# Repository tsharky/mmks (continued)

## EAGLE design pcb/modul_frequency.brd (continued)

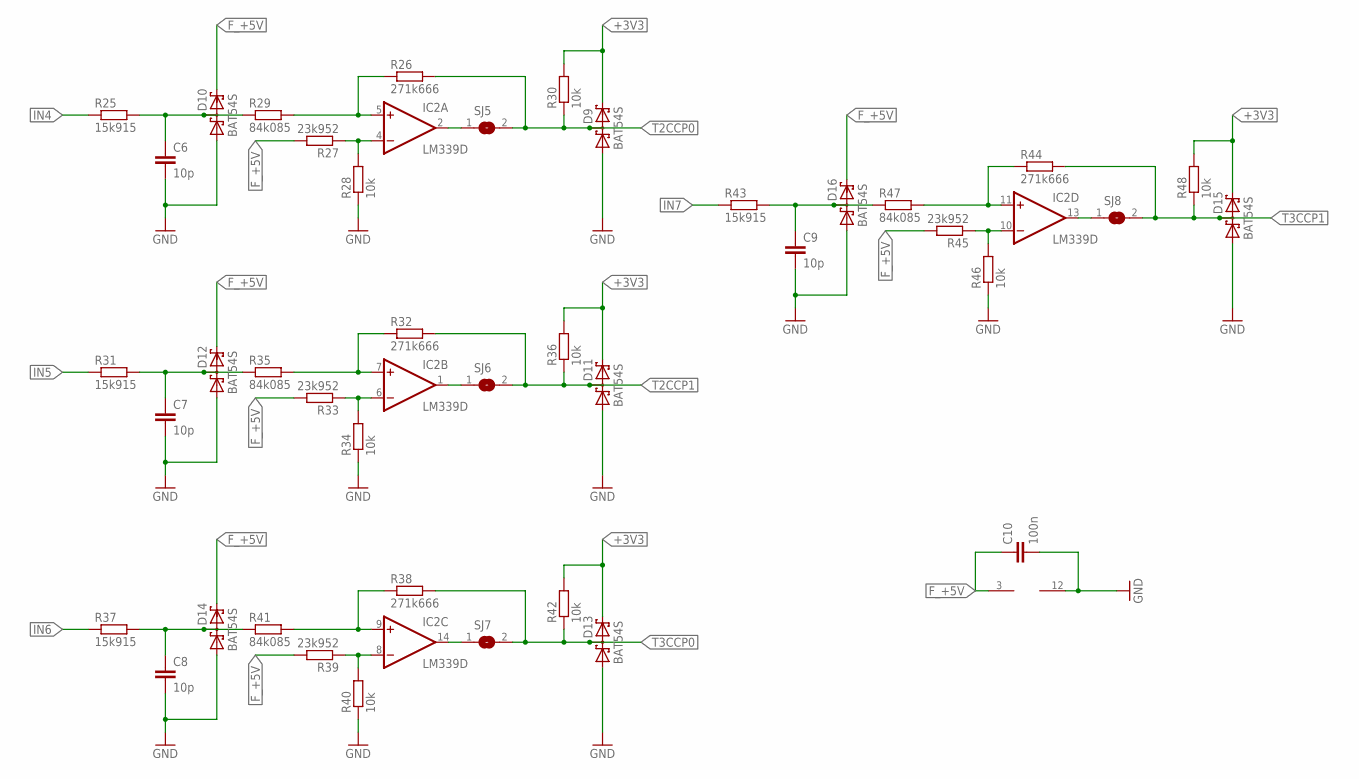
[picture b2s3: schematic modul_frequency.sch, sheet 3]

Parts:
C6, C7, C8, C9: 10p; C0805
C10: 100n; C0805
D9, D10, D11, D12, D13, D14, D15, D16: BAT54S; SOT23
IC2: LM339D; SO14
R25, R31, R37, R43: 15k915; R0805
R26, R32, R38, R44: 271k666; R0805
R27, R33, R39, R45: 23k952; R0805
R28, R30, R34, R36, R40, R42, R46, R48: 10k; R0805
R29, R35, R41, R47: 84k085; R0805
SJ5, SJ6, SJ7, SJ8: SJ

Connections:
+3V3: D9.2 (C2), D11.2 (C2), D13.2 (C2), D15.2 (C2), R30.2, R36.2, R42.2, R48.2; also elsewhere on the board
F_+5V: C10.1, D10.2 (C2), D12.2 (C2), D14.2 (C2), D16.2 (C2), IC2.3 (V+), R27.2, R33.2, R39.2, R45.2; also elsewhere on the board
GND: C6.2, C7.2, C8.2, C9.2, C10.2, D9.1 (A1), D10.1 (A1), D11.1 (A1), D12.1 (A1), D13.1 (A1), D14.1 (A1), D15.1 (A1), D16.1 (A1), IC2.12 (GND), R28.1, R34.1, R40.1, R46.1; also elsewhere on the board
IN4: R25.1; also elsewhere on the board
IN5: R31.1; also elsewhere on the board
IN6: R37.1; also elsewhere on the board
IN7: R43.1; also elsewhere on the board
unnamed: IC2.5 (+IN), R26.1, R29.2
unnamed: IC2.4 (-IN), R27.1, R28.2
unnamed: C6.1, D10.3 (C1A2), R25.2, R29.1
unnamed: IC2.7 (+IN), R32.1, R35.2
unnamed: IC2.6 (-IN), R33.1, R34.2
unnamed: C7.1, D12.3 (C1A2), R31.2, R35.1
unnamed: IC2.1 (OUT), SJ6.1
unnamed: IC2.9 (+IN), R38.1, R41.2
unnamed: IC2.8 (-IN), R39.1, R40.2
unnamed: C8.1, D14.3 (C1A2), R37.2, R41.1
unnamed: IC2.14 (OUT), SJ7.1
unnamed: IC2.11 (+IN), R44.1, R47.2
unnamed: IC2.10 (-IN), R45.1, R46.2
unnamed: C9.1, D16.3 (C1A2), R43.2, R47.1
unnamed: IC2.13 (OUT), SJ8.1
unnamed: IC2.2 (OUT), SJ5.1
T2CCP0: D9.3 (C1A2), R26.2, R30.1, SJ5.2; also elsewhere on the board
T2CCP1: D11.3 (C1A2), R32.2, R36.1, SJ6.2; also elsewhere on the board
T3CCP0: D13.3 (C1A2), R38.2, R42.1, SJ7.2; also elsewhere on the board
T3CCP1: D15.3 (C1A2), R44.2, R48.1, SJ8.2; also elsewhere on the board

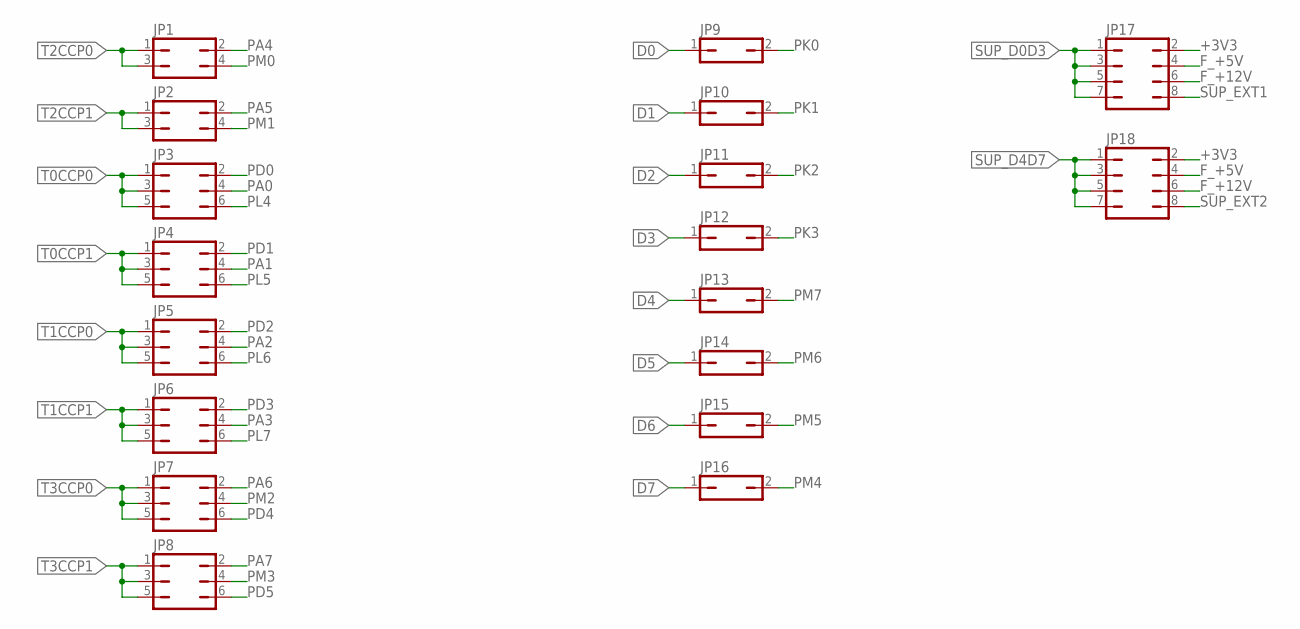
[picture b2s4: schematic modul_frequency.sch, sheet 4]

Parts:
JP1, JP2: JP2Q
JP3, JP4, JP5, JP6, JP7, JP8: JP3Q
JP9, JP10, JP11, JP12, JP13, JP14, JP15, JP16: JP1Q; JP1
JP17, JP18: JP4Q

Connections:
+3V3: JP17.2, JP18.2; also elsewhere on the board
D0: JP9.1; also elsewhere on the board
D1: JP10.1; also elsewhere on the board
D2: JP11.1; also elsewhere on the board
D3: JP12.1; also elsewhere on the board
D4: JP13.1; also elsewhere on the board
D5: JP14.1; also elsewhere on the board
D6: JP15.1; also elsewhere on the board
D7: JP16.1; also elsewhere on the board
F_+5V: JP17.4, JP18.4; also elsewhere on the board
F_+12V: JP17.6, JP18.6; also elsewhere on the board
PA0: JP3.4; also elsewhere on the board
PA1: JP4.4; also elsewhere on the board
PA2: JP5.4; also elsewhere on the board
PA3: JP6.4; also elsewhere on the board
PA4: JP1.2; also elsewhere on the board
PA5: JP2.2; also elsewhere on the board
PA6: JP7.2; also elsewhere on the board
PA7: JP8.2; also elsewhere on the board
PD0: JP3.2; also elsewhere on the board
PD1: JP4.2; also elsewhere on the board
PD2: JP5.2; also elsewhere on the board
PD3: JP6.2; also elsewhere on the board
PD4: JP7.6; also elsewhere on the board
PD5: JP8.6; also elsewhere on the board
PK0: JP9.2; also elsewhere on the board
PK1: JP10.2; also elsewhere on the board
PK2: JP11.2; also elsewhere on the board
PK3: JP12.2; also elsewhere on the board
PL4: JP3.6; also elsewhere on the board
PL5: JP4.6; also elsewhere on the board
PL6: JP5.6
PL7: JP6.6
PM0: JP1.4; also elsewhere on the board
PM1: JP2.4; also elsewhere on the board
PM2: JP7.4; also elsewhere on the board
PM3: JP8.4; also elsewhere on the board
PM4: JP16.2; also elsewhere on the board
PM5: JP15.2; also elsewhere on the board
PM6: JP14.2; also elsewhere on the board
PM7: JP13.2; also elsewhere on the board
SUP_D0D3: JP17.1, JP17.3, JP17.5, JP17.7; also elsewhere on the board
SUP_D4D7: JP18.1, JP18.3, JP18.5, JP18.7; also elsewhere on the board
SUP_EXT1: JP17.8; also elsewhere on the board
SUP_EXT2: JP18.8; also elsewhere on the board
T0CCP0: JP3.1, JP3.3, JP3.5; also elsewhere on the board
T0CCP1: JP4.1, JP4.3, JP4.5; also elsewhere on the board
T1CCP0: JP5.1, JP5.3, JP5.5; also elsewhere on the board
T1CCP1: JP6.1, JP6.3, JP6.5; also elsewhere on the board
T2CCP0: JP1.1, JP1.3; also elsewhere on the board
T2CCP1: JP2.1, JP2.3; also elsewhere on the board
T3CCP0: JP7.1, JP7.3, JP7.5; also elsewhere on the board
T3CCP1: JP8.1, JP8.3, JP8.5; also elsewhere on the board

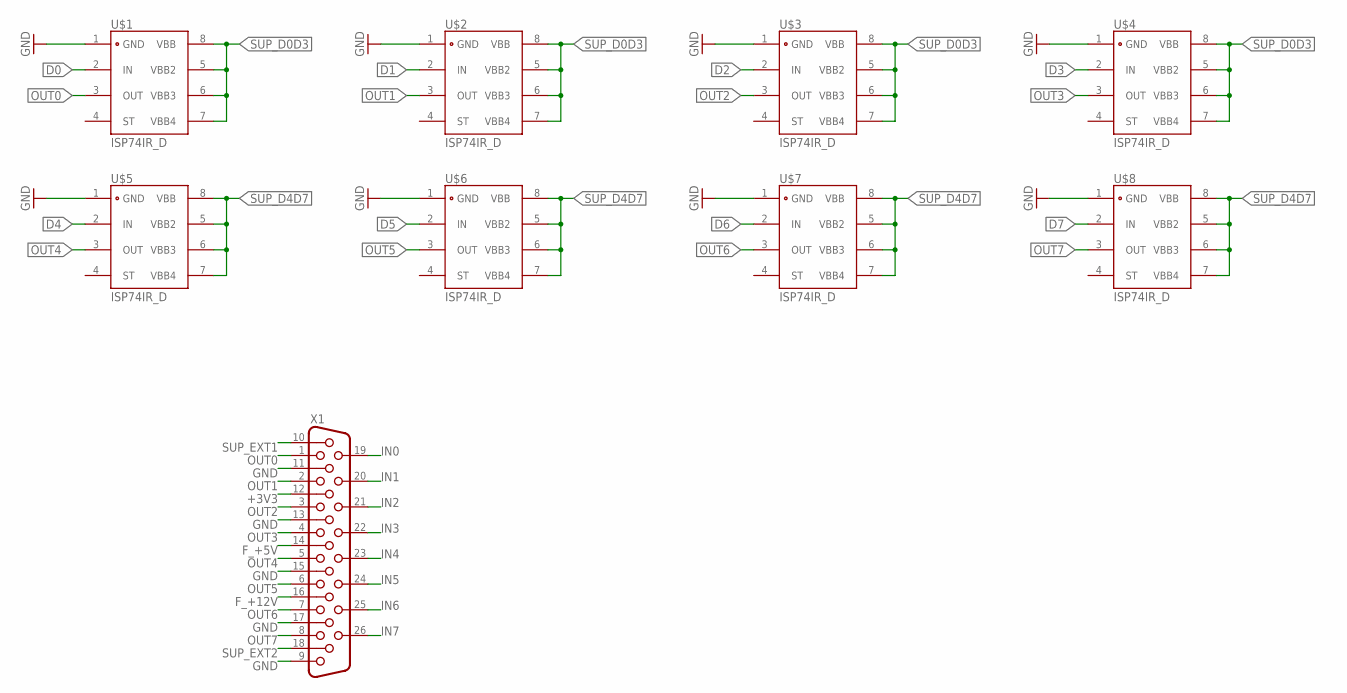
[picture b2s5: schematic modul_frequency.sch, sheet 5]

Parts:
U$1, U$2, U$3, U$4, U$5, U$6, U$7, U$8: ISP74IR_D; SO08
X1: HF26H; HDF26H

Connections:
+3V3: X1.12; also elsewhere on the board
D0: U$1.2 (IN); also elsewhere on the board
D1: U$2.2 (IN); also elsewhere on the board
D2: U$3.2 (IN); also elsewhere on the board
D3: U$4.2 (IN); also elsewhere on the board
D4: U$5.2 (IN); also elsewhere on the board
D5: U$6.2 (IN); also elsewhere on the board
D6: U$7.2 (IN); also elsewhere on the board
D7: U$8.2 (IN); also elsewhere on the board
F_+5V: X1.14; also elsewhere on the board
F_+12V: X1.16; also elsewhere on the board
GND: U$1.1 (GND), U$2.1 (GND), U$3.1 (GND), U$4.1 (GND), U$5.1 (GND), U$6.1 (GND), U$7.1 (GND), U$8.1 (GND), X1.9, X1.11, X1.13, X1.15, X1.17; also elsewhere on the board
IN0: X1.19; also elsewhere on the board
IN1: X1.20; also elsewhere on the board
IN2: X1.21; also elsewhere on the board
IN3: X1.22; also elsewhere on the board
IN4: X1.23; also elsewhere on the board
IN5: X1.24; also elsewhere on the board
IN6: X1.25; also elsewhere on the board
IN7: X1.26; also elsewhere on the board
OUT0: U$1.3 (OUT), X1.1
OUT1: U$2.3 (OUT), X1.2
OUT2: U$3.3 (OUT), X1.3
OUT3: U$4.3 (OUT), X1.4
OUT4: U$5.3 (OUT), X1.5
OUT5: U$6.3 (OUT), X1.6
OUT6: U$7.3 (OUT), X1.7
OUT7: U$8.3 (OUT), X1.8
SUP_D0D3: U$1.5 (VBB2), U$1.6 (VBB3), U$1.7 (VBB4), U$1.8 (VBB), U$2.5 (VBB2), U$2.6 (VBB3), U$2.7 (VBB4), U$2.8 (VBB), U$3.5 (VBB2), U$3.6 (VBB3), U$3.7 (VBB4), U$3.8 (VBB), U$4.5 (VBB2), U$4.6 (VBB3), U$4.7 (VBB4), U$4.8 (VBB); also elsewhere on the board
SUP_D4D7: U$5.5 (VBB2), U$5.6 (VBB3), U$5.7 (VBB4), U$5.8 (VBB), U$6.5 (VBB2), U$6.6 (VBB3), U$6.7 (VBB4), U$6.8 (VBB), U$7.5 (VBB2), U$7.6 (VBB3), U$7.7 (VBB4), U$7.8 (VBB), U$8.5 (VBB2), U$8.6 (VBB3), U$8.7 (VBB4), U$8.8 (VBB); also elsewhere on the board
SUP_EXT1: X1.10; also elsewhere on the board
SUP_EXT2: X1.18; also elsewhere on the board

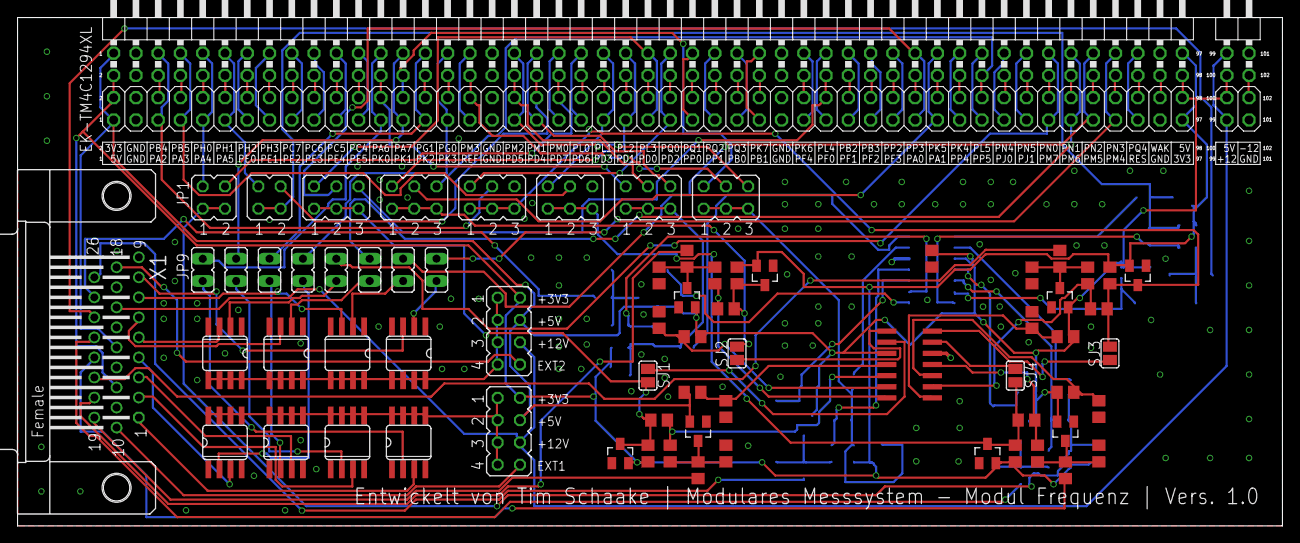
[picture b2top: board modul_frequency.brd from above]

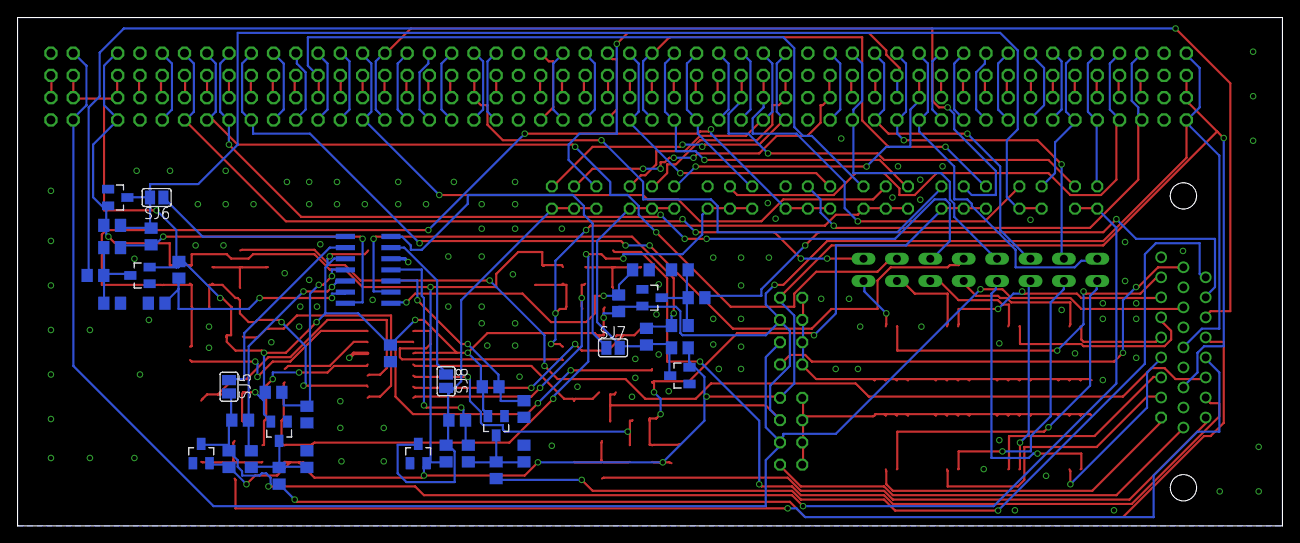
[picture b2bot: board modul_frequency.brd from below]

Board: 2 copper layers, 144.3 x 58.0 mm, 113 parts (42 on the bottom side), 160 nets.

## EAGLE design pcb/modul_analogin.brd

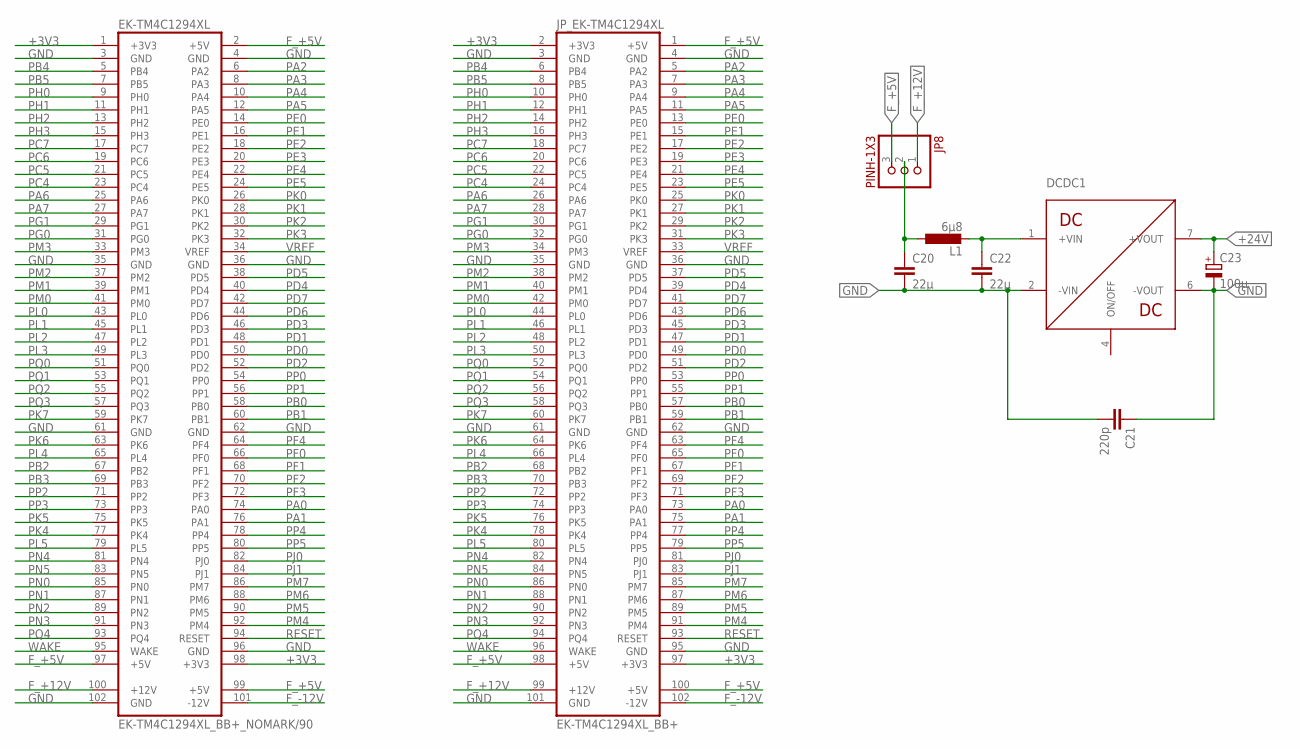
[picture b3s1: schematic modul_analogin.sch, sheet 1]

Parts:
C20, C22: 22µ; C1206
C21: 220p; C1808
C23: 100µ; E2,5-6
DCDC1: TDN3WI; TDN_XWI
EK-TM4C1294XL: EK-TM4C1294XL_BB+_NOMARK/90
JP8: PINH-1X3; 1X3
JP_EK-TM4C1294XL: EK-TM4C1294XL_BB+
L1: 6µ8; L1812

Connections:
+3V3: EK-TM4C1294XL.1 (+3V3), EK-TM4C1294XL.98 (+3V3), JP_EK-TM4C1294XL.2 (+3V3), JP_EK-TM4C1294XL.97 (+3V3); also elsewhere on the board
+24V: C23.+, DCDC1.7 (+VOUT); also elsewhere on the board
+VIN: C22.1, DCDC1.1 (+VIN), L1.2
F_+5V: EK-TM4C1294XL.2 (+5V), EK-TM4C1294XL.97 (+5V), EK-TM4C1294XL.99 (+5V), JP8.3, JP_EK-TM4C1294XL.1 (+5V), JP_EK-TM4C1294XL.98 (+5V), JP_EK-TM4C1294XL.100 (+5V); also elsewhere on the board
F_+12V: EK-TM4C1294XL.100 (+12V), JP8.1, JP_EK-TM4C1294XL.99 (+12V); also elsewhere on the board
F_-12V: EK-TM4C1294XL.101 (-12V), JP_EK-TM4C1294XL.102 (-12V); also elsewhere on the board
GND: C20.2, C21.1, C21.2, C22.2, C23.-, DCDC1.2 (-VIN), DCDC1.6 (-VOUT), EK-TM4C1294XL.3 (GND), EK-TM4C1294XL.4 (GND), EK-TM4C1294XL.35 (GND), EK-TM4C1294XL.36 (GND), EK-TM4C1294XL.61 (GND), EK-TM4C1294XL.62 (GND), EK-TM4C1294XL.96 (GND), EK-TM4C1294XL.102 (GND), JP_EK-TM4C1294XL.3 (GND), JP_EK-TM4C1294XL.4 (GND), JP_EK-TM4C1294XL.35 (GND), JP_EK-TM4C1294XL.36 (GND), JP_EK-TM4C1294XL.61 (GND), JP_EK-TM4C1294XL.62 (GND), JP_EK-TM4C1294XL.95 (GND), JP_EK-TM4C1294XL.101 (GND); also elsewhere on the board
unnamed: C20.1, JP8.2, L1.1
PA0: EK-TM4C1294XL.74 (PA0), JP_EK-TM4C1294XL.73 (PA0)
PA1: EK-TM4C1294XL.76 (PA1), JP_EK-TM4C1294XL.75 (PA1)
PA2: EK-TM4C1294XL.6 (PA2), JP_EK-TM4C1294XL.5 (PA2)
PA3: EK-TM4C1294XL.8 (PA3), JP_EK-TM4C1294XL.7 (PA3)
PA4: EK-TM4C1294XL.10 (PA4), JP_EK-TM4C1294XL.9 (PA4)
PA5: EK-TM4C1294XL.12 (PA5), JP_EK-TM4C1294XL.11 (PA5)
PA6: EK-TM4C1294XL.25 (PA6), JP_EK-TM4C1294XL.26 (PA6)
PA7: EK-TM4C1294XL.27 (PA7), JP_EK-TM4C1294XL.28 (PA7)
PB0: EK-TM4C1294XL.58 (PB0), JP_EK-TM4C1294XL.57 (PB0)
PB1: EK-TM4C1294XL.60 (PB1), JP_EK-TM4C1294XL.59 (PB1)
PB2: EK-TM4C1294XL.67 (PB2), JP_EK-TM4C1294XL.68 (PB2)
PB3: EK-TM4C1294XL.69 (PB3), JP_EK-TM4C1294XL.70 (PB3)
PB4: EK-TM4C1294XL.5 (PB4), JP_EK-TM4C1294XL.6 (PB4); also elsewhere on the board
PB5: EK-TM4C1294XL.7 (PB5), JP_EK-TM4C1294XL.8 (PB5); also elsewhere on the board
PC4: EK-TM4C1294XL.23 (PC4), JP_EK-TM4C1294XL.24 (PC4)
PC5: EK-TM4C1294XL.21 (PC5), JP_EK-TM4C1294XL.22 (PC5)
PC6: EK-TM4C1294XL.19 (PC6), JP_EK-TM4C1294XL.20 (PC6)
PC7: EK-TM4C1294XL.17 (PC7), JP_EK-TM4C1294XL.18 (PC7)
PD0: EK-TM4C1294XL.50 (PD0), JP_EK-TM4C1294XL.49 (PD0); also elsewhere on the board
PD1: EK-TM4C1294XL.48 (PD1), JP_EK-TM4C1294XL.47 (PD1); also elsewhere on the board
PD2: EK-TM4C1294XL.52 (PD2), JP_EK-TM4C1294XL.51 (PD2); also elsewhere on the board
PD3: EK-TM4C1294XL.46 (PD3), JP_EK-TM4C1294XL.45 (PD3); also elsewhere on the board
PD4: EK-TM4C1294XL.40 (PD4), JP_EK-TM4C1294XL.39 (PD4); also elsewhere on the board
PD5: EK-TM4C1294XL.38 (PD5), JP_EK-TM4C1294XL.37 (PD5); also elsewhere on the board
PD6: EK-TM4C1294XL.44 (PD6), JP_EK-TM4C1294XL.43 (PD6); also elsewhere on the board
PD7: EK-TM4C1294XL.42 (PD7), JP_EK-TM4C1294XL.41 (PD7); also elsewhere on the board
PE0: EK-TM4C1294XL.14 (PE0), JP_EK-TM4C1294XL.13 (PE0); also elsewhere on the board
PE1: EK-TM4C1294XL.16 (PE1), JP_EK-TM4C1294XL.15 (PE1); also elsewhere on the board
PE2: EK-TM4C1294XL.18 (PE2), JP_EK-TM4C1294XL.17 (PE2); also elsewhere on the board
PE3: EK-TM4C1294XL.20 (PE3), JP_EK-TM4C1294XL.19 (PE3); also elsewhere on the board
PE4: EK-TM4C1294XL.22 (PE4), JP_EK-TM4C1294XL.21 (PE4); also elsewhere on the board
PE5: EK-TM4C1294XL.24 (PE5), JP_EK-TM4C1294XL.23 (PE5); also elsewhere on the board
PF0: EK-TM4C1294XL.66 (PF0), JP_EK-TM4C1294XL.65 (PF0)
PF1: EK-TM4C1294XL.68 (PF1), JP_EK-TM4C1294XL.67 (PF1)
PF2: EK-TM4C1294XL.70 (PF2), JP_EK-TM4C1294XL.69 (PF2)
PF3: EK-TM4C1294XL.72 (PF3), JP_EK-TM4C1294XL.71 (PF3)
PF4: EK-TM4C1294XL.64 (PF4), JP_EK-TM4C1294XL.63 (PF4)
PG0: EK-TM4C1294XL.31 (PG0), JP_EK-TM4C1294XL.32 (PG0)
PG1: EK-TM4C1294XL.29 (PG1), JP_EK-TM4C1294XL.30 (PG1)
PH0: EK-TM4C1294XL.9 (PH0), JP_EK-TM4C1294XL.10 (PH0)
PH1: EK-TM4C1294XL.11 (PH1), JP_EK-TM4C1294XL.12 (PH1)
PH2: EK-TM4C1294XL.13 (PH2), JP_EK-TM4C1294XL.14 (PH2)
PH3: EK-TM4C1294XL.15 (PH3), JP_EK-TM4C1294XL.16 (PH3)
PJ0: EK-TM4C1294XL.82 (PJ0), JP_EK-TM4C1294XL.81 (PJ0)
PJ1: EK-TM4C1294XL.84 (PJ1), JP_EK-TM4C1294XL.83 (PJ1)
PK0: EK-TM4C1294XL.26 (PK0), JP_EK-TM4C1294XL.25 (PK0)
PK1: EK-TM4C1294XL.28 (PK1), JP_EK-TM4C1294XL.27 (PK1)
PK2: EK-TM4C1294XL.30 (PK2), JP_EK-TM4C1294XL.29 (PK2)
PK3: EK-TM4C1294XL.32 (PK3), JP_EK-TM4C1294XL.31 (PK3)
PK4: EK-TM4C1294XL.77 (PK4), JP_EK-TM4C1294XL.78 (PK4)
PK5: EK-TM4C1294XL.75 (PK5), JP_EK-TM4C1294XL.76 (PK5)
PK6: EK-TM4C1294XL.63 (PK6), JP_EK-TM4C1294XL.64 (PK6)
PK7: EK-TM4C1294XL.59 (PK7), JP_EK-TM4C1294XL.60 (PK7)
PL0: EK-TM4C1294XL.43 (PL0), JP_EK-TM4C1294XL.44 (PL0)
PL1: EK-TM4C1294XL.45 (PL1), JP_EK-TM4C1294XL.46 (PL1)
PL2: EK-TM4C1294XL.47 (PL2), JP_EK-TM4C1294XL.48 (PL2)
PL3: EK-TM4C1294XL.49 (PL3), JP_EK-TM4C1294XL.50 (PL3)
PL4: EK-TM4C1294XL.65 (PL4), JP_EK-TM4C1294XL.66 (PL4)
PL5: EK-TM4C1294XL.79 (PL5), JP_EK-TM4C1294XL.80 (PL5)
PM0: EK-TM4C1294XL.41 (PM0), JP_EK-TM4C1294XL.42 (PM0)
PM1: EK-TM4C1294XL.39 (PM1), JP_EK-TM4C1294XL.40 (PM1)
PM2: EK-TM4C1294XL.37 (PM2), JP_EK-TM4C1294XL.38 (PM2)
PM3: EK-TM4C1294XL.33 (PM3), JP_EK-TM4C1294XL.34 (PM3)
PM4: EK-TM4C1294XL.92 (PM4), JP_EK-TM4C1294XL.91 (PM4)
PM5: EK-TM4C1294XL.90 (PM5), JP_EK-TM4C1294XL.89 (PM5)
PM6: EK-TM4C1294XL.88 (PM6), JP_EK-TM4C1294XL.87 (PM6)
PM7: EK-TM4C1294XL.86 (PM7), JP_EK-TM4C1294XL.85 (PM7)
PN0: EK-TM4C1294XL.85 (PN0), JP_EK-TM4C1294XL.86 (PN0)
PN1: EK-TM4C1294XL.87 (PN1), JP_EK-TM4C1294XL.88 (PN1)
PN2: EK-TM4C1294XL.89 (PN2), JP_EK-TM4C1294XL.90 (PN2)
PN3: EK-TM4C1294XL.91 (PN3), JP_EK-TM4C1294XL.92 (PN3)
PN4: EK-TM4C1294XL.81 (PN4), JP_EK-TM4C1294XL.82 (PN4)
PN5: EK-TM4C1294XL.83 (PN5), JP_EK-TM4C1294XL.84 (PN5)
PP0: EK-TM4C1294XL.54 (PP0), JP_EK-TM4C1294XL.53 (PP0)
PP1: EK-TM4C1294XL.56 (PP1), JP_EK-TM4C1294XL.55 (PP1)
PP2: EK-TM4C1294XL.71 (PP2), JP_EK-TM4C1294XL.72 (PP2)
PP3: EK-TM4C1294XL.73 (PP3), JP_EK-TM4C1294XL.74 (PP3)
PP4: EK-TM4C1294XL.78 (PP4), JP_EK-TM4C1294XL.77 (PP4)
PP5: EK-TM4C1294XL.80 (PP5), JP_EK-TM4C1294XL.79 (PP5)
PQ0: EK-TM4C1294XL.51 (PQ0), JP_EK-TM4C1294XL.52 (PQ0)
PQ1: EK-TM4C1294XL.53 (PQ1), JP_EK-TM4C1294XL.54 (PQ1)
PQ2: EK-TM4C1294XL.55 (PQ2), JP_EK-TM4C1294XL.56 (PQ2)
PQ3: EK-TM4C1294XL.57 (PQ3), JP_EK-TM4C1294XL.58 (PQ3)
PQ4: EK-TM4C1294XL.93 (PQ4), JP_EK-TM4C1294XL.94 (PQ4)
RESET: EK-TM4C1294XL.94 (RESET), JP_EK-TM4C1294XL.93 (RESET)
VREF: EK-TM4C1294XL.34 (VREF), JP_EK-TM4C1294XL.33 (VREF)
WAKE: EK-TM4C1294XL.95 (WAKE), JP_EK-TM4C1294XL.96 (WAKE)

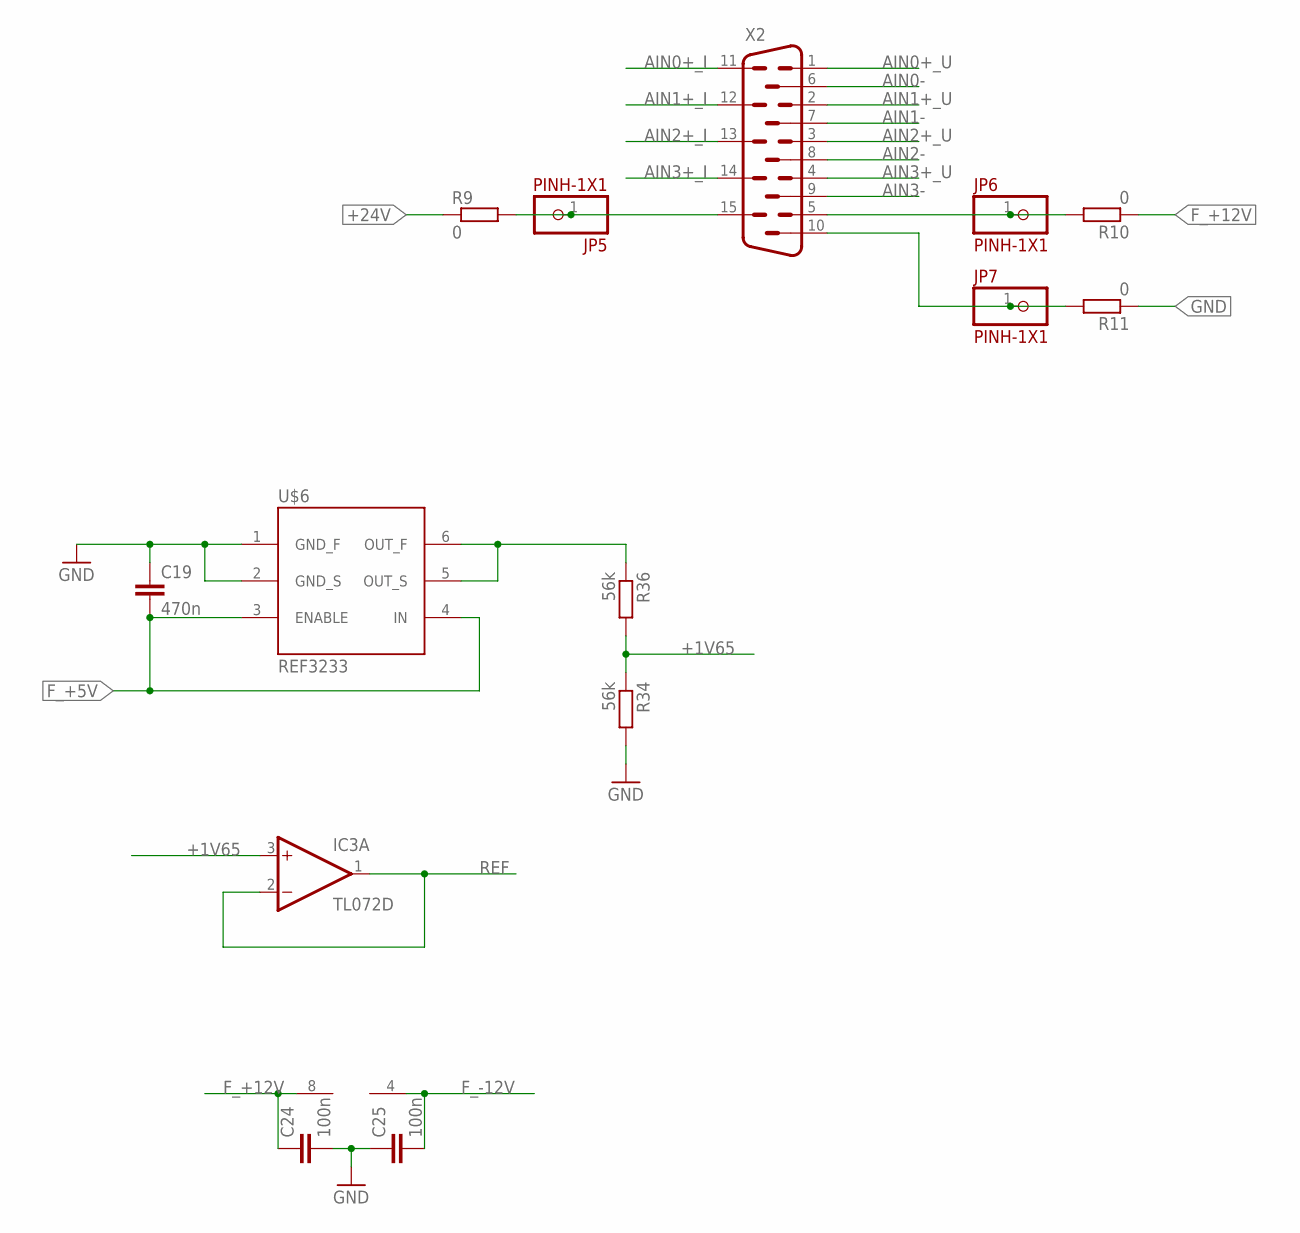
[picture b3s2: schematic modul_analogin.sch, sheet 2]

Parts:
C19: 470n; C0805
C24, C25: 100n; C0805
IC3: TL072D; SO08
JP5, JP6, JP7: PINH-1X1; 1X1
R9, R10, R11: 0; R0805
R34, R36: 56k; R0805
U$6: REF3233; SOT-23-6_DBV
X2: HM15H; HDM15H

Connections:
+1V65: IC3.3 (+IN), R34.1, R36.2
+24V: R9.1; also elsewhere on the board
AIN0+_I: X2.11; also elsewhere on the board
AIN0+_U: X2.1; also elsewhere on the board
AIN0-: X2.6; also elsewhere on the board
AIN1+_I: X2.12; also elsewhere on the board
AIN1+_U: X2.2; also elsewhere on the board
AIN1-: X2.7; also elsewhere on the board
AIN2+_I: X2.13; also elsewhere on the board
AIN2+_U: X2.3; also elsewhere on the board
AIN2-: X2.8; also elsewhere on the board
AIN3+_I: X2.14; also elsewhere on the board
AIN3+_U: X2.4; also elsewhere on the board
AIN3-: X2.9; also elsewhere on the board
F_+5V: C19.2, U$6.3 (ENABLE), U$6.4 (IN); also elsewhere on the board
F_+12V: C24.1, IC3.8 (V+), R10.1; also elsewhere on the board
F_-12V: C25.2, IC3.4 (V-); also elsewhere on the board
GND: C19.1, C24.2, C25.1, R11.1, R34.2, U$6.1 (GND_F), U$6.2 (GND_S); also elsewhere on the board
unnamed: R36.1, U$6.5 (OUT_S), U$6.6 (OUT_F)
REF: IC3.1 (OUT), IC3.2 (-IN); also elsewhere on the board
SUP_1: JP5.1, R9.2, X2.15
SUP_2: JP6.1, R10.2, X2.5
SUP_3: JP7.1, R11.2, X2.10

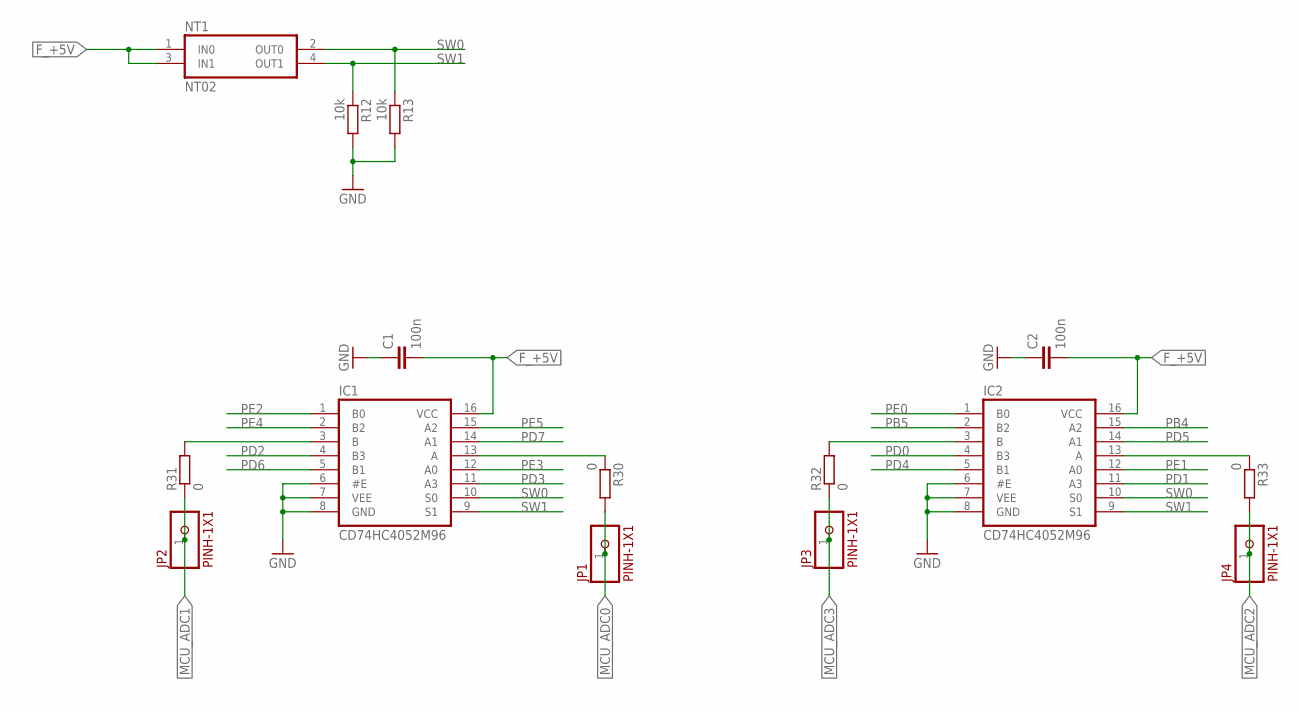
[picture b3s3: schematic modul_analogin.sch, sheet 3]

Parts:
C1, C2: 100n; C0805
IC1, IC2: CD74HC4052M96; SOIC16_D
JP1, JP2, JP3, JP4: PINH-1X1; 1X1
NT1: NT02
R12, R13: 10k; R0805
R30, R31, R32, R33: 0; R0805

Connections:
F_+5V: C1.2, C2.2, IC1.16 (VCC), IC2.16 (VCC), NT1.1 (IN0), NT1.3 (IN1); also elsewhere on the board
GND: C1.1, C2.1, IC1.6 (#E), IC1.7 (VEE), IC1.8 (GND), IC2.6 (#E), IC2.7 (VEE), IC2.8 (GND), R12.2, R13.2; also elsewhere on the board
MCU_ADC0: JP1.1, R30.2; also elsewhere on the board
MCU_ADC1: JP2.1, R31.1; also elsewhere on the board
MCU_ADC2: JP4.1, R33.2; also elsewhere on the board
MCU_ADC3: JP3.1, R32.1; also elsewhere on the board
unnamed: IC1.13 (A), R30.1
unnamed: IC2.3 (B), R32.2
unnamed: IC1.3 (B), R31.2
unnamed: IC2.13 (A), R33.1
PB4: IC2.15 (A2); also elsewhere on the board
PB5: IC2.2 (B2); also elsewhere on the board
PD0: IC2.4 (B3); also elsewhere on the board
PD1: IC2.11 (A3); also elsewhere on the board
PD2: IC1.4 (B3); also elsewhere on the board
PD3: IC1.11 (A3); also elsewhere on the board
PD4: IC2.5 (B1); also elsewhere on the board
PD5: IC2.14 (A1); also elsewhere on the board
PD6: IC1.5 (B1); also elsewhere on the board
PD7: IC1.14 (A1); also elsewhere on the board
PE0: IC2.1 (B0); also elsewhere on the board
PE1: IC2.12 (A0); also elsewhere on the board
PE2: IC1.1 (B0); also elsewhere on the board
PE3: IC1.12 (A0); also elsewhere on the board
PE4: IC1.2 (B2); also elsewhere on the board
PE5: IC1.15 (A2); also elsewhere on the board
SW0: IC1.10 (S0), IC2.10 (S0), NT1.2 (OUT0), R13.1
SW1: IC1.9 (S1), IC2.9 (S1), NT1.4 (OUT1), R12.1

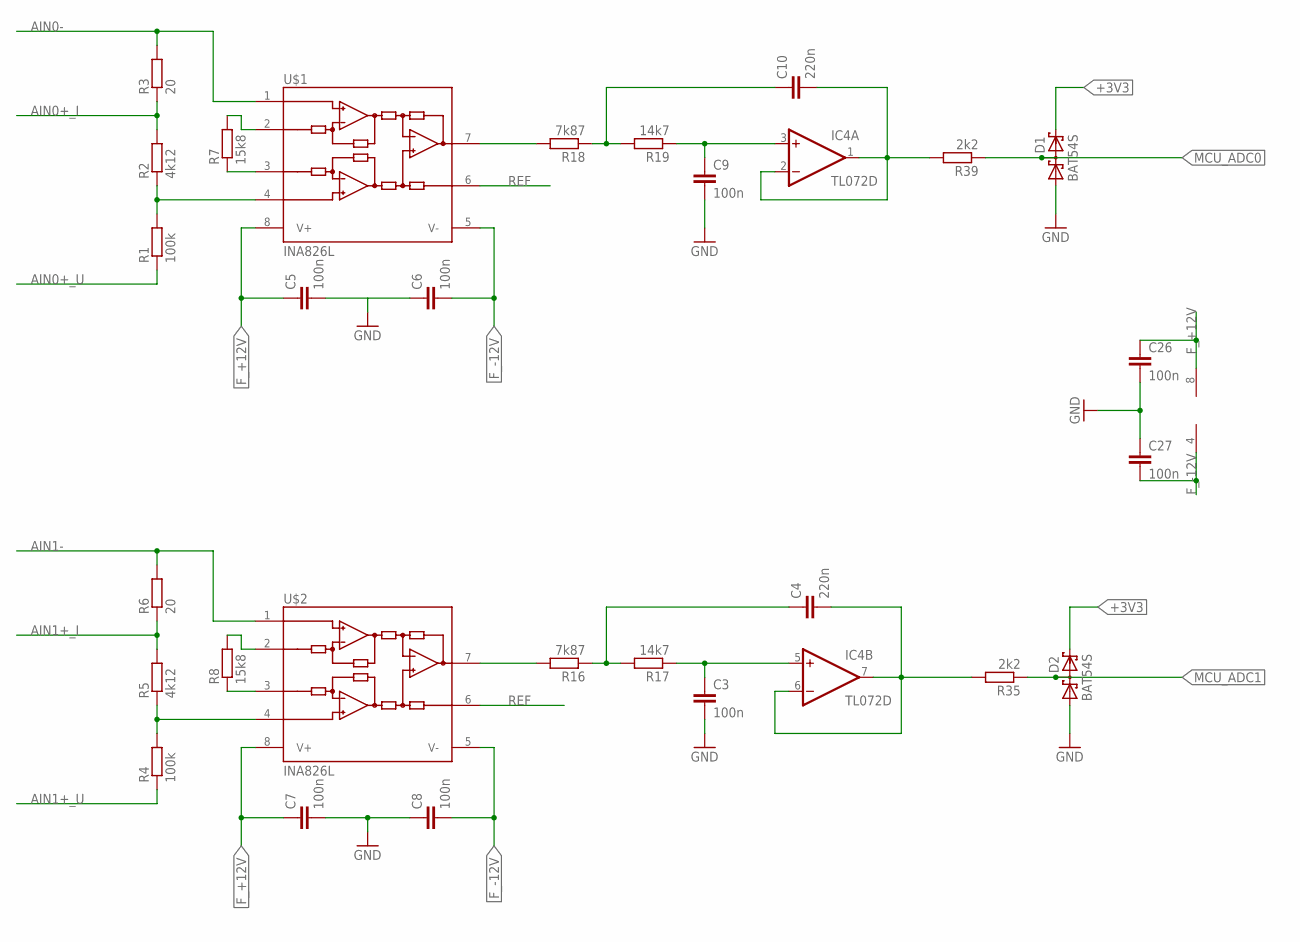
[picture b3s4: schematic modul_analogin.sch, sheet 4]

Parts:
C3, C5, C6, C7, C8, C9, C26, C27: 100n; C0805
C4, C10: 220n; C0805
D1, D2: BAT54S; SOT23
IC4: TL072D; SO08
R1, R4: 100k; R0805
R2, R5: 4k12; R0805
R3, R6: 20; R0805
R7, R8: 15k8; R0805
R16, R18: 7k87; R0805
R17, R19: 14k7; R0805
R35, R39: 2k2; R0805
U$1, U$2: INA826L; DGK_S-PDSO-G8

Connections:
+3V3: D1.2 (C2), D2.2 (C2); also elsewhere on the board
AIN0+_I: R2.2, R3.1; also elsewhere on the board
AIN0+_U: R1.1; also elsewhere on the board
AIN0-: R3.2, U$1.1 (-IN); also elsewhere on the board
AIN1+_I: R5.2, R6.1; also elsewhere on the board
AIN1+_U: R4.1; also elsewhere on the board
AIN1-: R6.2, U$2.1 (-IN); also elsewhere on the board
F_+12V: C5.1, C7.1, C26.1, IC4.8 (V+), U$1.8 (V+), U$2.8 (V+); also elsewhere on the board
F_-12V: C6.2, C8.2, C27.2, IC4.4 (V-), U$1.5 (V-), U$2.5 (V-); also elsewhere on the board
GND: C3.2, C7.2, C8.1, C9.2, C26.2, C27.1, D1.1 (A1), D2.1 (A1); also elsewhere on the board
MCU_ADC0: D1.3 (C1A2), R39.1; also elsewhere on the board
MCU_ADC1: D2.3 (C1A2), R35.1; also elsewhere on the board
unnamed: C9.1, IC4.3 (+IN), R19.1
unnamed: R7.1, U$1.3 (J)
unnamed: R7.2, U$1.2 (J)
unnamed: R8.1, U$2.3 (J)
unnamed: R8.2, U$2.2 (J)
unnamed: C5.2, C6.1
unnamed: R4.2, R5.1, U$2.4 (+IN)
unnamed: R16.2, U$2.7 (OUT)
unnamed: C4.1, R16.1, R17.2
unnamed: R18.2, U$1.7 (OUT)
unnamed: C10.1, R18.1, R19.2
unnamed: C3.1, IC4.5 (+IN), R17.1
unnamed: R1.2, R2.1, U$1.4 (+IN)
unnamed: C10.2, IC4.1 (OUT), IC4.2 (-IN), R39.2
unnamed: C4.2, IC4.6 (-IN), IC4.7 (OUT), R35.2
REF: U$1.6 (REF), U$2.6 (REF); also elsewhere on the board

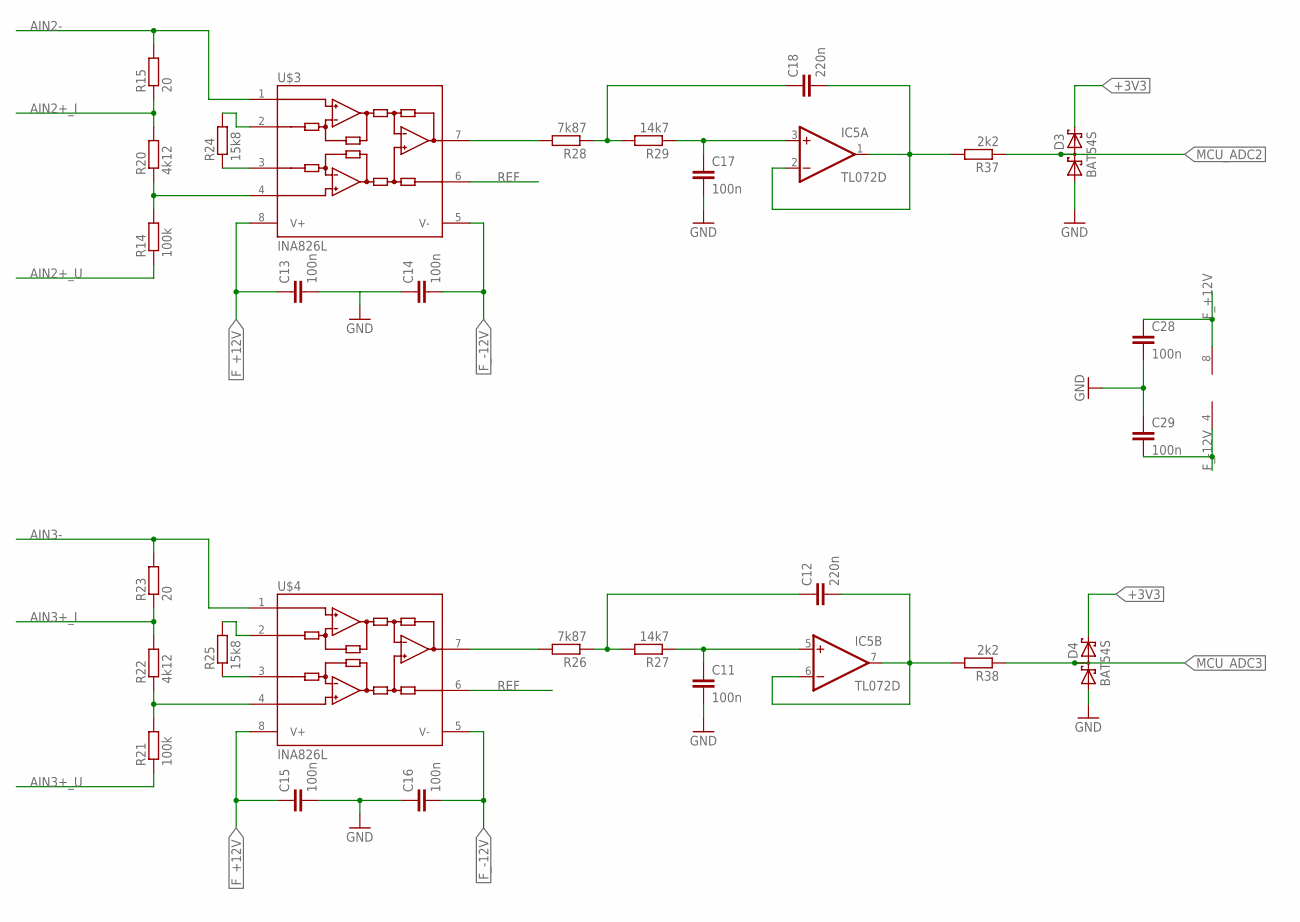
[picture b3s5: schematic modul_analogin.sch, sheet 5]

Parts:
C11, C13, C14, C15, C16, C17, C28, C29: 100n; C0805
C12, C18: 220n; C0805
D3, D4: BAT54S; SOT23
IC5: TL072D; SO08
R14, R21: 100k; R0805
R15, R23: 20; R0805
R20, R22: 4k12; R0805
R24, R25: 15k8; R0805
R26, R28: 7k87; R0805
R27, R29: 14k7; R0805
R37, R38: 2k2; R0805
U$3, U$4: INA826L; DGK_S-PDSO-G8

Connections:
+3V3: D3.2 (C2), D4.2 (C2); also elsewhere on the board
AIN2+_I: R15.1, R20.2; also elsewhere on the board
AIN2+_U: R14.1; also elsewhere on the board
AIN2-: R15.2, U$3.1 (-IN); also elsewhere on the board
AIN3+_I: R22.2, R23.1; also elsewhere on the board
AIN3+_U: R21.1; also elsewhere on the board
AIN3-: R23.2, U$4.1 (-IN); also elsewhere on the board
F_+12V: C13.1, C15.1, C28.1, IC5.8 (V+), U$3.8 (V+), U$4.8 (V+); also elsewhere on the board
F_-12V: C14.2, C16.2, C29.2, IC5.4 (V-), U$3.5 (V-), U$4.5 (V-); also elsewhere on the board
GND: C11.2, C15.2, C16.1, C17.2, C28.2, C29.1, D3.1 (A1), D4.1 (A1); also elsewhere on the board
MCU_ADC2: D3.3 (C1A2), R37.1; also elsewhere on the board
MCU_ADC3: D4.3 (C1A2), R38.1; also elsewhere on the board
unnamed: R14.2, R20.1, U$3.4 (+IN)
unnamed: R24.1, U$3.3 (J)
unnamed: R24.2, U$3.2 (J)
unnamed: C13.2, C14.1
unnamed: R25.1, U$4.3 (J)
unnamed: R25.2, U$4.2 (J)
unnamed: R21.2, R22.1, U$4.4 (+IN)
unnamed: R26.2, U$4.7 (OUT)
unnamed: C17.1, IC5.3 (+IN), R29.1
unnamed: C12.1, R26.1, R27.2
unnamed: R28.2, U$3.7 (OUT)
unnamed: C18.1, R28.1, R29.2
unnamed: C11.1, IC5.5 (+IN), R27.1
unnamed: C12.2, IC5.6 (-IN), IC5.7 (OUT), R38.2
unnamed: C18.2, IC5.1 (OUT), IC5.2 (-IN), R37.2
REF: U$3.6 (REF), U$4.6 (REF); also elsewhere on the board
